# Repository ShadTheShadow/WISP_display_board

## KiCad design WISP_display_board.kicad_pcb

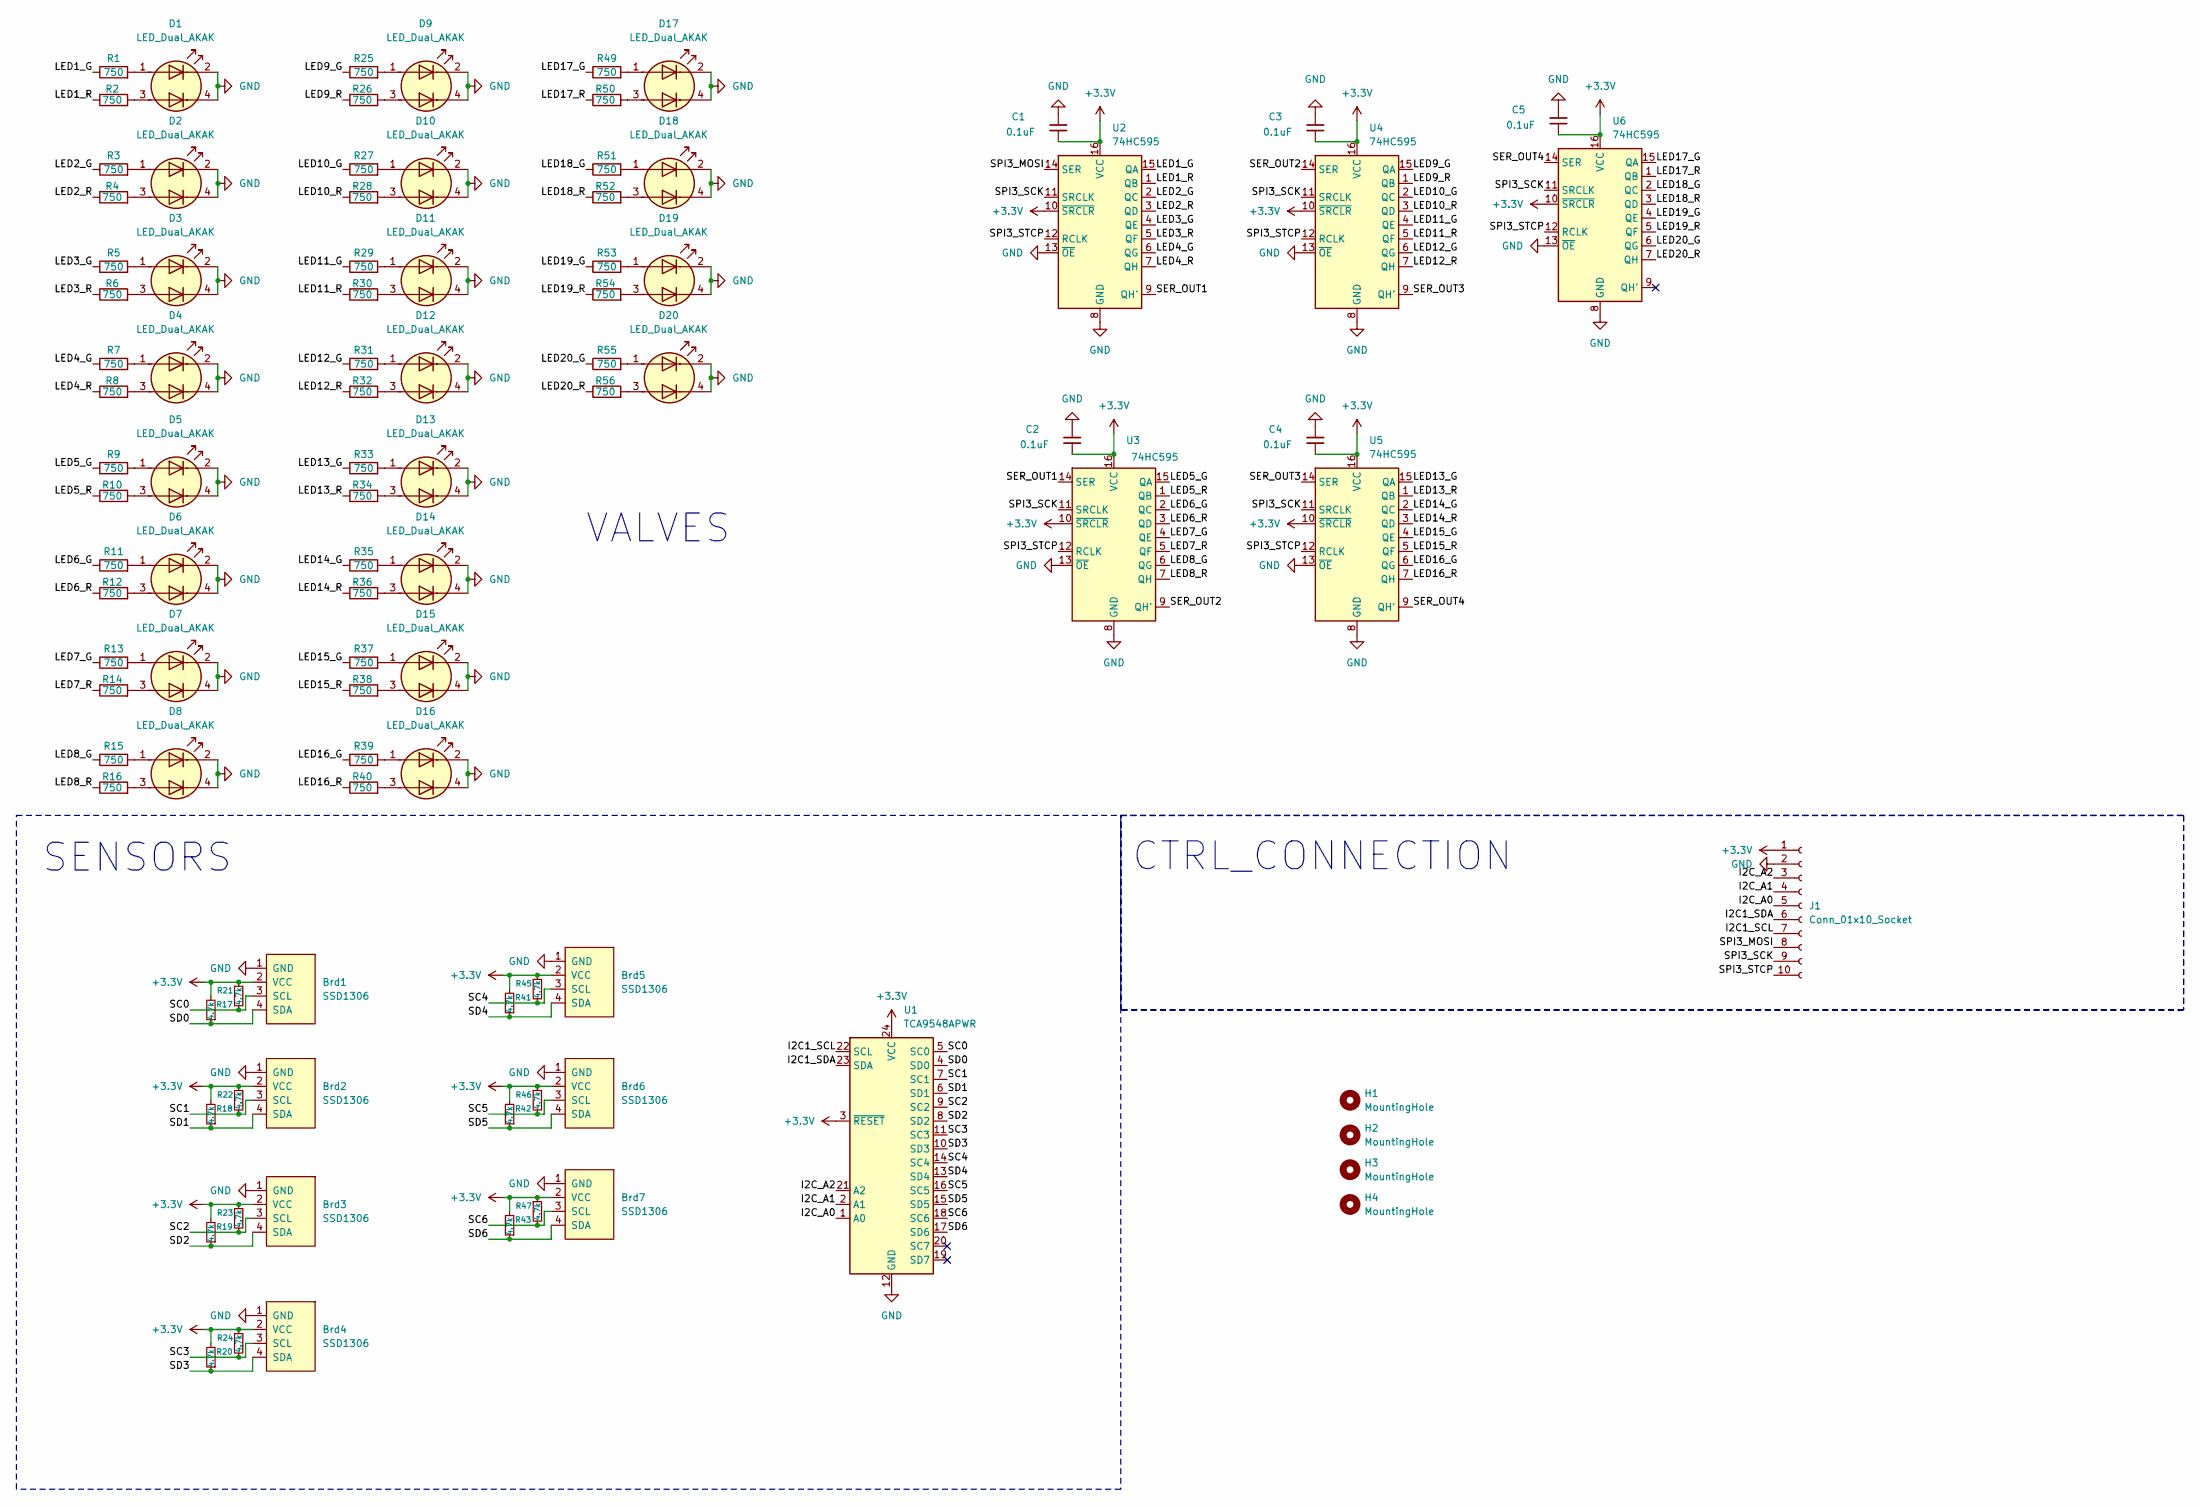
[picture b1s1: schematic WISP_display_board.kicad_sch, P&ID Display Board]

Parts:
Brd1, Brd2, Brd3, Brd4, Brd5, Brd6, Brd7: SSD1306; ssd1306_custom_edited
C1, C2, C3, C4, C5: 0.1uF; C_0805_2012Metric_Pad1.18x1.45mm_HandSolder
D1, D2, D3, D4, D5, D6, D7, D8, D9, D10, D11, D12, D13, D14, D15, D16, D17, D18, D19, D20: LED_Dual_AKAK; LED_Kingbright_KPBD-3224
H1, H2, H3, H4: MountingHole; MountingHole_3.2mm_M3
J1: Conn_01x10_Socket; PinSocket_1x10_P2.54mm_Vertical
R1, R2, R3, R4, R5, R6, R7, R8, R9, R10, R11, R12, R13, R14, R15, R16, R25, R26, R27, R28, R29, R30, R31, R32, R33, R34, R35, R36, R37, R38, R39, R40, R49, R50, R51, R52, R53, R54, R55, R56: 750; R_0805_2012Metric_Pad1.20x1.40mm_HandSolder
R17, R18, R19, R20, R21, R22, R23, R24, R41, R42, R43, R45, R46, R47: 4.7k; R_0805_2012Metric_Pad1.20x1.40mm_HandSolder
U1: TCA9548APWR; TSSOP-24_4.4x7.8mm_P0.65mm
U2, U3, U4, U5, U6: 74HC595; SOIC-16W_7.5x12.8mm_P1.27mm

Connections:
+3.3V: Brd1.2 (VCC), Brd2.2 (VCC), Brd3.2 (VCC), Brd4.2 (VCC), Brd5.2 (VCC), Brd6.2 (VCC), Brd7.2 (VCC), C1.2, C2.2, C3.2, C4.2, C5.2, J1.1, R17.2, R18.2, R19.2, R20.2, R21.1, R22.1, R23.1, R24.1, R41.2, R42.2, R43.2, R45.1, R46.1, R47.1, U1.3 (~RESET), U1.24 (VCC), U2.10 (~SRCLR), U2.16 (VCC), U3.10 (~SRCLR), U3.16 (VCC), U4.10 (~SRCLR), U4.16 (VCC), U5.10 (~SRCLR), U5.16 (VCC), U6.10 (~SRCLR), U6.16 (VCC)
/I2C1_SCL: J1.7, U1.22 (SCL)
/I2C1_SDA: J1.6, U1.23 (SDA)
/I2C_A0: J1.5, U1.1 (A0)
/I2C_A1: J1.4, U1.2 (A1)
/I2C_A2: J1.3, U1.21 (A2)
/LED1_G: R1.1, U2.15 (QA)
/LED1_R: R2.1, U2.1 (QB)
/LED2_G: R3.1, U2.2 (QC)
/LED2_R: R4.1, U2.3 (QD)
/LED3_G: R5.1, U2.4 (QE)
/LED3_R: R6.1, U2.5 (QF)
/LED4_G: R7.1, U2.6 (QG)
/LED4_R: R8.1, U2.7 (QH)
/LED5_G: R9.1, U3.15 (QA)
/LED5_R: R10.1, U3.1 (QB)
/LED6_G: R11.1, U3.2 (QC)
/LED6_R: R12.1, U3.3 (QD)
/LED7_G: R13.1, U3.4 (QE)
/LED7_R: R14.1, U3.5 (QF)
/LED8_G: R15.1, U3.6 (QG)
/LED8_R: R16.1, U3.7 (QH)
/LED9_G: R25.1, U4.15 (QA)
/LED9_R: R26.1, U4.1 (QB)
/LED10_G: R27.1, U4.2 (QC)
/LED10_R: R28.1, U4.3 (QD)
/LED11_G: R29.1, U4.4 (QE)
/LED11_R: R30.1, U4.5 (QF)
/LED12_G: R31.1, U4.6 (QG)
/LED12_R: R32.1, U4.7 (QH)
/LED13_G: R33.1, U5.15 (QA)
/LED13_R: R34.1, U5.1 (QB)
/LED14_G: R35.1, U5.2 (QC)
/LED14_R: R36.1, U5.3 (QD)
/LED15_G: R37.1, U5.4 (QE)
/LED15_R: R38.1, U5.5 (QF)
/LED16_G: R39.1, U5.6 (QG)
/LED16_R: R40.1, U5.7 (QH)
/LED17_G: R49.1, U6.15 (QA)
/LED17_R: R50.1, U6.1 (QB)
/LED18_G: R51.1, U6.2 (QC)
/LED18_R: R52.1, U6.3 (QD)
/LED19_G: R53.1, U6.4 (QE)
/LED19_R: R54.1, U6.5 (QF)
/LED20_G: R55.1, U6.6 (QG)
/LED20_R: R56.1, U6.7 (QH)
/SC0: Brd1.3 (SCL), R21.2, U1.5 (SC0)
/SC1: Brd2.3 (SCL), R22.2, U1.7 (SC1)
/SC2: Brd3.3 (SCL), R23.2, U1.9 (SC2)
/SC3: Brd4.3 (SCL), R24.2, U1.11 (SC3)
/SC4: Brd5.3 (SCL), R45.2, U1.14 (SC4)
/SC5: Brd6.3 (SCL), R46.2, U1.16 (SC5)
/SC6: Brd7.3 (SCL), R47.2, U1.18 (SC6)
/SD0: Brd1.4 (SDA), R17.1, U1.4 (SD0)
/SD1: Brd2.4 (SDA), R18.1, U1.6 (SD1)
/SD2: Brd3.4 (SDA), R19.1, U1.8 (SD2)
/SD3: Brd4.4 (SDA), R20.1, U1.10 (SD3)
/SD4: Brd5.4 (SDA), R41.1, U1.13 (SD4)
/SD5: Brd6.4 (SDA), R42.1, U1.15 (SD5)
/SD6: Brd7.4 (SDA), R43.1, U1.17 (SD6)
/SER_OUT1: U2.9 (QH'), U3.14 (SER)
/SER_OUT2: U3.9 (QH'), U4.14 (SER)
/SER_OUT3: U4.9 (QH'), U5.14 (SER)
/SER_OUT4: U5.9 (QH'), U6.14 (SER)
/SPI3_MOSI: J1.8, U2.14 (SER)
/SPI3_SCK: J1.9, U2.11 (SRCLK), U3.11 (SRCLK), U4.11 (SRCLK), U5.11 (SRCLK), U6.11 (SRCLK)
/SPI3_STCP: J1.10, U2.12 (RCLK), U3.12 (RCLK), U4.12 (RCLK), U5.12 (RCLK), U6.12 (RCLK)
GND: Brd1.1 (GND), Brd2.1 (GND), Brd3.1 (GND), Brd4.1 (GND), Brd5.1 (GND), Brd6.1 (GND), Brd7.1 (GND), C1.1, C2.1, C3.1, C4.1, C5.1, D1.2 (K1), D1.4 (K2), D2.2 (K1), D2.4 (K2), D3.2 (K1), D3.4 (K2), D4.2 (K1), D4.4 (K2), D5.2 (K1), D5.4 (K2), D6.2 (K1), D6.4 (K2), D7.2 (K1), D7.4 (K2), D8.2 (K1), D8.4 (K2), D9.2 (K1), D9.4 (K2), D10.2 (K1), D10.4 (K2), D11.2 (K1), D11.4 (K2), D12.2 (K1), D12.4 (K2), D13.2 (K1), D13.4 (K2), D14.2 (K1), D14.4 (K2), D15.2 (K1), D15.4 (K2), D16.2 (K1), D16.4 (K2), D17.2 (K1), D17.4 (K2), D18.2 (K1), D18.4 (K2), D19.2 (K1), D19.4 (K2), D20.2 (K1), D20.4 (K2), J1.2, U1.12 (GND), U2.8 (GND), U2.13 (~OE), U3.8 (GND), U3.13 (~OE), U4.8 (GND), U4.13 (~OE), U5.8 (GND), U5.13 (~OE), U6.8 (GND), U6.13 (~OE)
unnamed: D1.1 (A1), R1.2
unnamed: D1.3 (A2), R2.2
unnamed: D2.1 (A1), R3.2
unnamed: D2.3 (A2), R4.2
unnamed: D3.1 (A1), R5.2
unnamed: D3.3 (A2), R6.2
unnamed: D4.1 (A1), R7.2
unnamed: D4.3 (A2), R8.2
unnamed: D5.1 (A1), R9.2
unnamed: D5.3 (A2), R10.2
unnamed: D6.1 (A1), R11.2
unnamed: D6.3 (A2), R12.2
unnamed: D7.1 (A1), R13.2
unnamed: D7.3 (A2), R14.2
unnamed: D8.1 (A1), R15.2
unnamed: D8.3 (A2), R16.2
unnamed: D9.1 (A1), R25.2
unnamed: D9.3 (A2), R26.2
unnamed: D10.1 (A1), R27.2
unnamed: D10.3 (A2), R28.2
unnamed: D11.1 (A1), R29.2
unnamed: D11.3 (A2), R30.2
unnamed: D12.1 (A1), R31.2
unnamed: D12.3 (A2), R32.2
unnamed: D13.1 (A1), R33.2
unnamed: D13.3 (A2), R34.2
unnamed: D14.1 (A1), R35.2
unnamed: D14.3 (A2), R36.2
unnamed: D15.1 (A1), R37.2
unnamed: D15.3 (A2), R38.2
unnamed: D16.1 (A1), R39.2
unnamed: D16.3 (A2), R40.2
unnamed: D17.1 (A1), R49.2
unnamed: D17.3 (A2), R50.2
unnamed: D18.1 (A1), R51.2
unnamed: D18.3 (A2), R52.2
unnamed: D19.1 (A1), R53.2
unnamed: D19.3 (A2), R54.2
unnamed: D20.1 (A1), R55.2
unnamed: D20.3 (A2), R56.2

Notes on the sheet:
CTRL_CONNECTION
VALVES
SENSORS

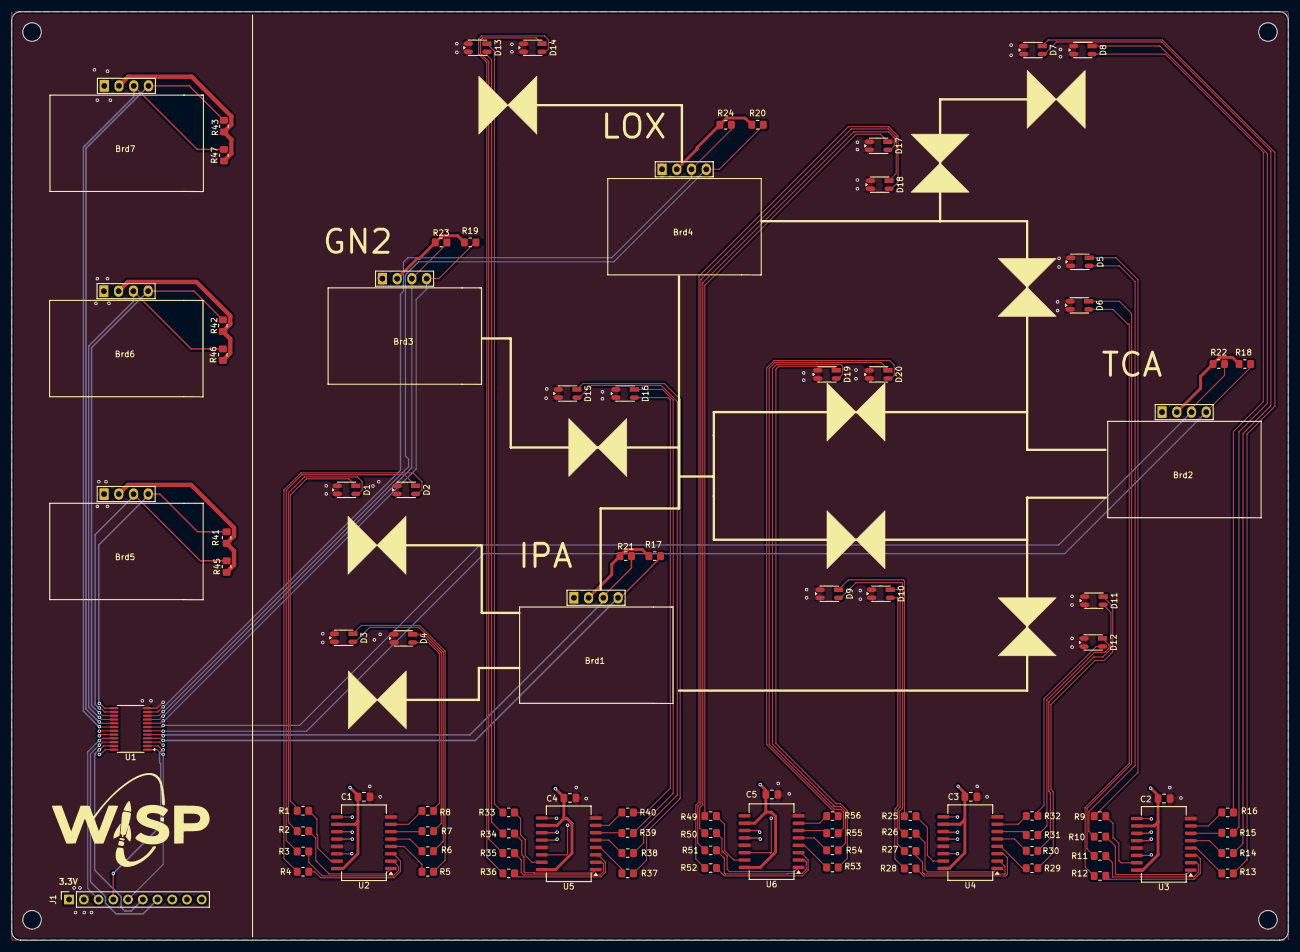
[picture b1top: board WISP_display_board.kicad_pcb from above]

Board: 4 copper layers, 220.0 x 160.0 mm, 97 parts (0 on the bottom side), 108 nets.

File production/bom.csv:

Designator,Footprint,Quantity,Value,LCSC Part #
"BRD1, BRD2, BRD3, BRD4, BRD5, BRD6, BRD7",ssd1306_custom_edited,7,SSD1306,
"C1, C2, C3, C4, C5",0805,5,0.1uF,
"D1, D10, D11, D12, D13, D14, D15, D16, D17, D18, D19, D2, D20, D3, D4, D5, D6, D7, D8, D9",LED_Kingbright_KPBD-3224,20,LED_Dual_AKAK,
J1,PinSocket_1x10_P2.54mm_Vertical,1,Conn_01x10_Socket,
"R1, R10, R11, R12, R13, R14, R15, R16, R2, R25, R26, R27, R28, R29, R3, R30, R31, R32, R33, R34, R35, R36, R37, R38, R39, R4, R40, R49, R5, R50, R51, R52, R53, R54, R55, R56, R6, R7, R8, R9",0805,40,750,
"R17, R18, R19, R20, R21, R22, R23, R24, R41, R42, R43, R45, R46, R47",0805,14,4.7k,
U1,TSSOP-24_4.4x7.8mm_P0.65mm,1,TCA9548APWR,
"U2, U3, U4, U5, U6",SOIC-16W_7.5x12.8mm_P1.27mm,5,74HC595,
